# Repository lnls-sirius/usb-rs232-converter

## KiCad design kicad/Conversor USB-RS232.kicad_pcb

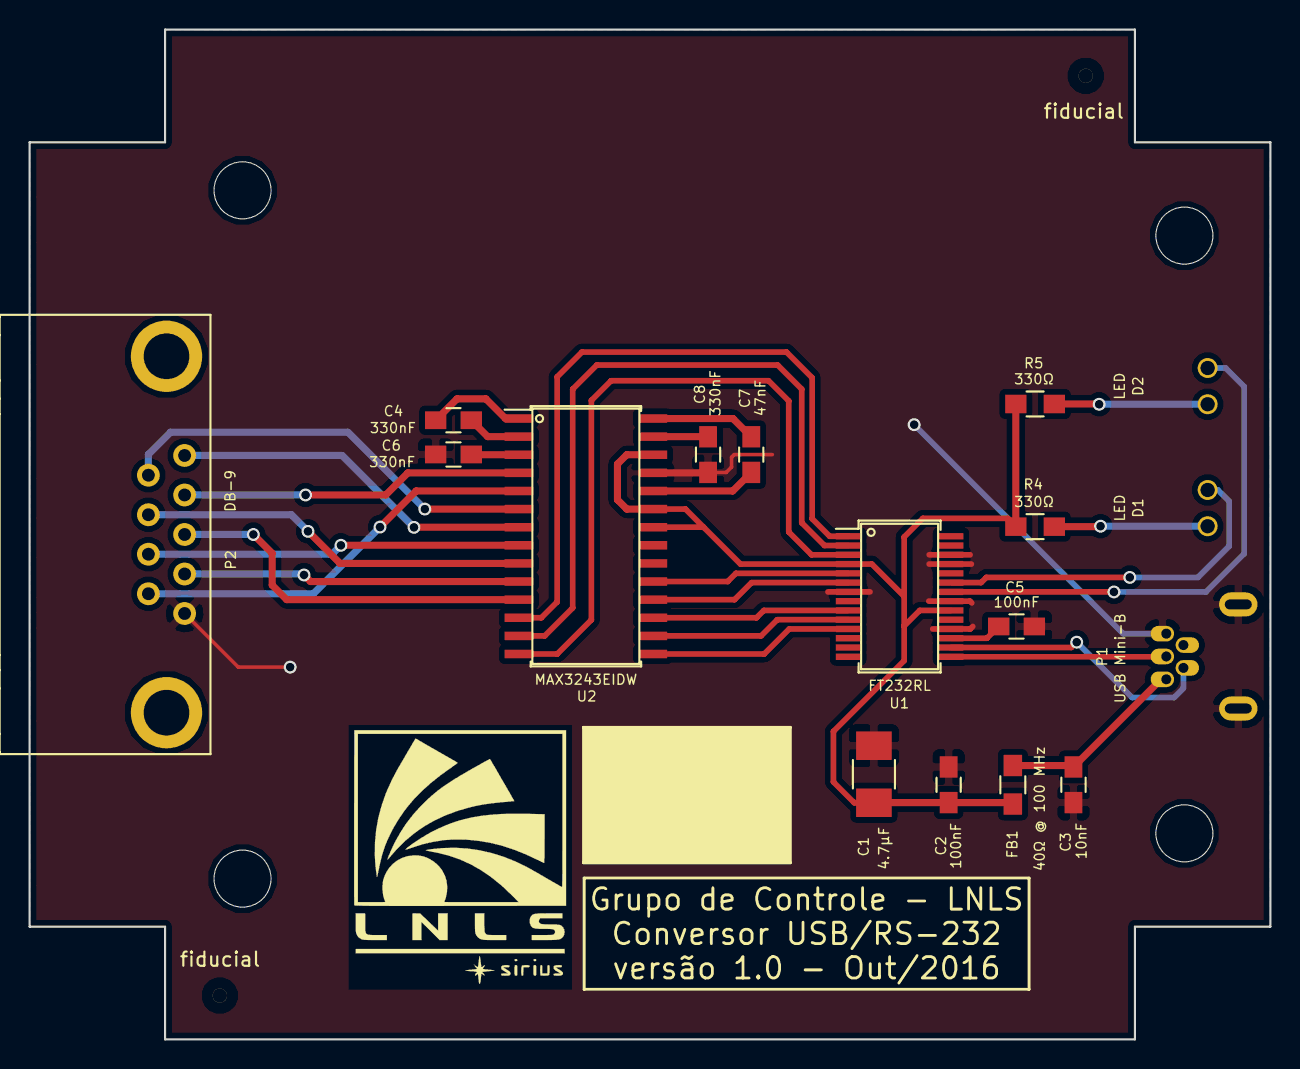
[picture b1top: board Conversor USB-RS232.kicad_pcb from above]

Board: 2 copper layers, 87.0 x 70.8 mm, 23 parts (0 on the bottom side), 32 nets.

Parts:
C1: 4.7µF; C_1210_HandSoldering
C2, C5: 100nF; C_0805_HandSoldering
C3: 10nF; C_0805_HandSoldering
C4, C6, C8: 330nF; C_0805_HandSoldering
C7: 47nF; C_0805_HandSoldering
D1, D2: LED; LED_para_painel_KINGBRIGHT
F1, F2, F3, F4: Furo de fixação (4mm); MountingHole_4mm
FB1: 40Ω @ 100 MHz; R_0805_HandSoldering
P1: USB Mini-B; USB_Mini-B
P2: DB-9; DB9_TE
R4, R5: 330Ω; R_0805_HandSoldering
U1: FT232RL; SSOP-28_5.3x10.2mm_Pitch0.65mm
U2: MAX3243EIDW; SOIC-28W_7.5x17.9mm_Pitch1.27mm
fiducial: Fiducial_1mm_Dia_2.54mm_Outer_CopperTop
fiducial#2: Fiducial_1mm_Dia_2.54mm_Outer_CopperTop

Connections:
+5V: C1.1, C2.1, FB1.1, R4.1, R5.1, U1.4, U1.20, U2.22, U2.23, U2.26
/CTS#: U1.11, U2.15
/DCD#: U1.10, U2.16
/DSR#: U1.9, U2.17
/DTR#: U1.2, U2.13
/P2_1: P2.1, U2.7
/P2_2: P2.2, U2.4
/P2_3: P2.3, U2.11
/P2_4: P2.4, U2.10
/P2_6: P2.6, U2.6
/P2_7: P2.7, U2.9
/P2_8: P2.8, U2.8
/P2_9: P2.9, U2.5
/RI#: U1.6, U2.18
/RTS#: U1.3, U2.14
/RXD: U1.5, U2.19
/RXLED#: D2.1, U1.22
/TXD: U1.1, U2.12
/TXLED#: D1.1, U1.23
/USB_D+: P1.3, U1.15
/USB_D-: P1.2, U1.16
GND: C1.2, C2.2, C3.2, C5.2, C6.2, C8.2, P1.5, P1.6, P1.7, P2.5, U1.7, U1.18, U1.21, U1.25, U1.26, U2.25
unnamed: C3.1, FB1.2, P1.1
unnamed: C4.1, U2.1
unnamed: C4.2, U2.2
unnamed: C5.1, U1.17
unnamed: C6.1, U2.3
unnamed: C7.1, U2.28
unnamed: C7.2, U2.24
unnamed: C8.1, U2.27
unnamed: D1.2, R4.2
unnamed: D2.2, R5.2

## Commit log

2019-04-09 repo migrated from CNPEM in-house GitLab
